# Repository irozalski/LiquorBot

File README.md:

# 🤖 LiquorBot

### Automatic liquor dispensing machine  used for pouring several-layer shots.<br> 
### The project uses a stepper motor, liquid pumps, Hall sensor, optocouplers and LEDs controlled by the Esp32 microcontroller. <br>
### Most of the case parts were printed on a 3D printer.
---
## Electronic schematic <br> 

---
## PCB 3D visualisation <br> 

---

## Render of project <br>

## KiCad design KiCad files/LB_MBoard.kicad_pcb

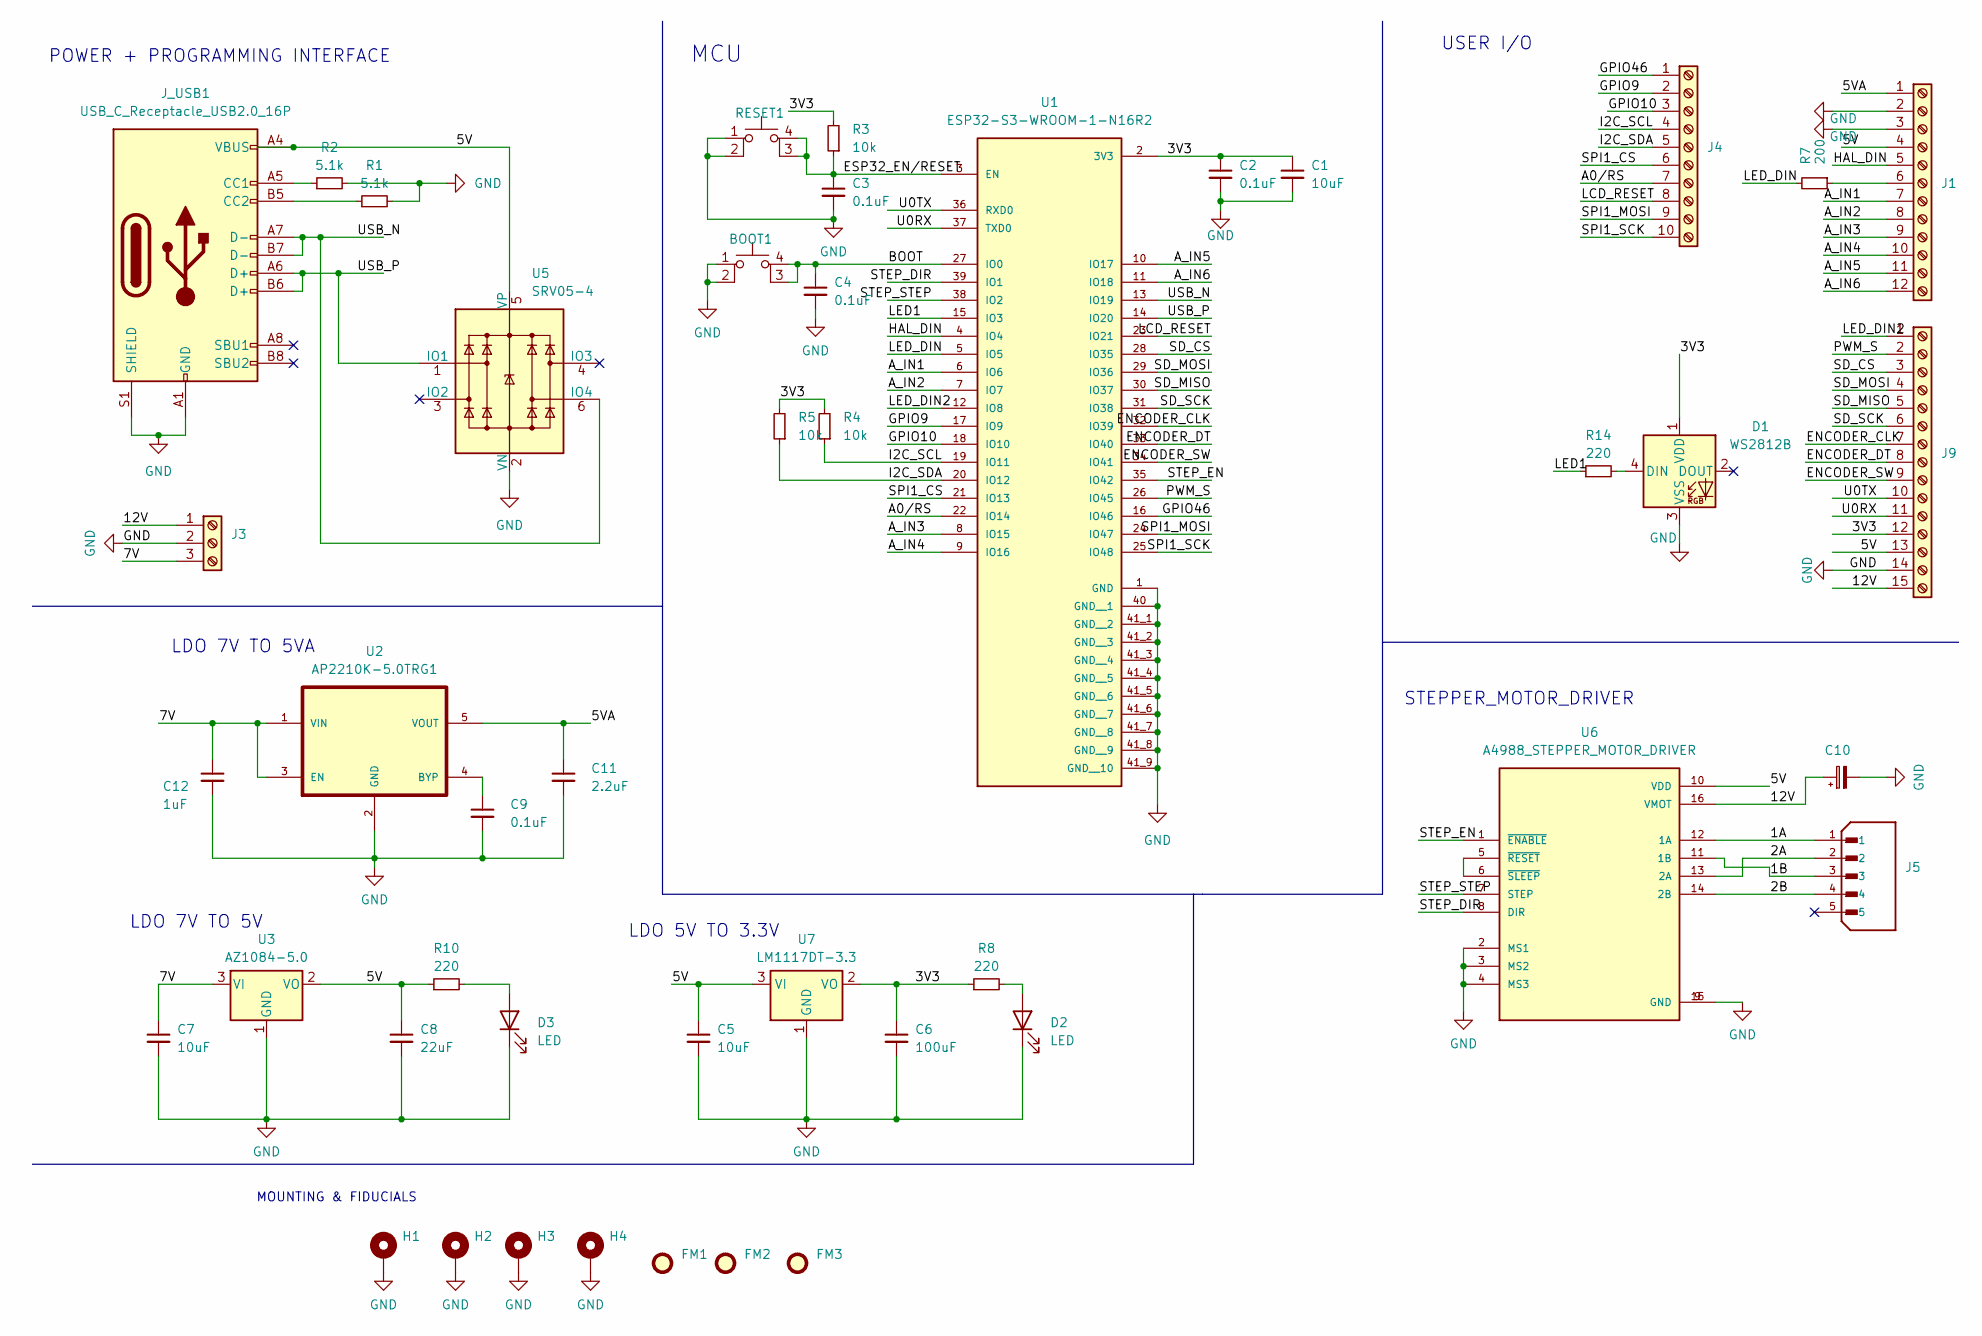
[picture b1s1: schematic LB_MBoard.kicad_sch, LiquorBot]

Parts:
BOOT1: SW_MEC_5E; SW_PTS_647_SN50_SMTR2_LFS
C1, C5, C7: 10uF; C_0805_2012Metric
C2, C3, C4, C9: 0.1uF; C_0805_2012Metric
C6: 100uF; C_0805_2012Metric
C8: 22uF; C_0805_2012Metric
C10: 100u; CAP_EEE1VA101XP
C11: 2.2uF; C_0805_2012Metric
C12: 1uF; C_0805_2012Metric
D1: WS2812B; LED_WS2812B_PLCC4_5.0x5.0mm_P3.2mm
D2, D3: LED; LED_0805_2012Metric
FM1, FM2, FM3: Fiducial; Fiducial_1mm_Mask2mm
H1, H2, H3, H4: MountingHole_Pad; MountingHole_3.2mm_M3_Pad_Via
J1: Screw_Terminal_01x12; 393570012
J3: Screw_Terminal_01x03; TerminalBlock_Phoenix_MKDS-1,5-3_1x03_P5.00mm_Horizontal
J4: Screw_Terminal_01x10; 393570010
J5: B5B-XH-A; JST_B5B-XH-A; PARTREV 7/4/21
J9: Screw_Terminal_01x15; 393570015
J_USB1: USB_C_Receptacle_USB2.0_16P; GCT_USB4085-GF-A_REVB
R1, R2: 5.1k; R_0805_2012Metric
R3, R4, R5: 10k; R_0805_2012Metric
R7: 200; R_0805_2012Metric
R8, R10, R14: 220; R_0805_2012Metric
RESET1: SW_MEC_5E; SW_PTS_647_SN50_SMTR2_LFS
U1: ESP32-S3-WROOM-1-N16R2; XCVR_ESP32-S3-WROOM-1U-N16; PARTREV v1.0
U2: AP2210K-5.0TRG1; SOT-23-5_RAW
U3: AZ1084-5.0; DPAK457P1010X238-3N
U5: SRV05-4; SOT-23-6
U6: A4988_STEPPER_MOTOR_DRIVER; MODULE_A4988_STEPPER_MOTOR_DRIVER_CARRIER
U7: LM1117DT-3.3; TO-252-3_TabPin2

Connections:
/1A: J5.1, U6.12 (1A)
/1B: J5.3, U6.11 (1B)
/2A: J5.2, U6.13 (2A)
/2B: J5.4, U6.14 (2B)
/3V3: C1.1, C2.1, C6.1, D1.1 (VDD), J9.12, R3.2, R4.2, R5.2, R8.1, U1.2 (3V3), U7.2 (VO)
/5V: C5.1, C8.1, J1.4, J9.13, J_USB1.A4 (VBUS), J_USB1.A9 (VBUS), J_USB1.B4 (VBUS), J_USB1.B9 (VBUS), R10.1, U3.2 (VO), U5.5 (VP), U6.10 (VDD), U7.3 (VI)
/5VA: C11.1, J1.1, U2.5 (VOUT)
/7V: C7.1, C12.1, J3.3, U2.1 (VIN), U2.3 (EN), U3.3 (VI)
/12V: C10.1, J3.1, J9.15, U6.16 (VMOT)
/A0/RS: J4.7, U1.22 (IO14)
/A_IN1: J1.7, U1.6 (IO6)
/A_IN2: J1.8, U1.7 (IO7)
/A_IN3: J1.9, U1.8 (IO15)
/A_IN4: J1.10, U1.9 (IO16)
/A_IN5: J1.11, U1.10 (IO17)
/A_IN6: J1.12, U1.11 (IO18)
/BOOT: BOOT1.3 (K), BOOT1.4 (A), C4.1, U1.27 (IO0); also elsewhere on the board
/ENCODER_CLK: J9.7, U1.32 (IO39)
/ENCODER_DT: J9.8, U1.33 (IO40)
/ENCODER_SW: J9.9, U1.34 (IO41)
/ESP32_EN/RESET: C3.1, R3.1, RESET1.3 (K), RESET1.4 (A), U1.3 (EN); also elsewhere on the board
/GPIO9: J4.2, U1.17 (IO9)
/GPIO10: J4.3, U1.18 (IO10)
/GPIO46: J4.1, U1.16 (IO46)
/HAL_DIN: J1.5, U1.4 (IO4)
/I2C_SCL: J4.4, R4.1, U1.19 (IO11)
/I2C_SDA: J4.5, R5.1, U1.20 (IO12)
/LCD_RESET: J4.8, U1.23 (IO21)
/LED1: R14.1, U1.15 (IO3)
/LED_DIN: R7.2, U1.5 (IO5)
/LED_DIN2: J9.1, U1.12 (IO8)
/PWM_S: J9.2, U1.26 (IO45)
/SD_CS: J9.3, U1.28 (IO35)
/SD_MISO: J9.5, U1.30 (IO37)
/SD_MOSI: J9.4, U1.29 (IO36)
/SD_SCK: J9.6, U1.31 (IO38)
/SPI1_CS: J4.6, U1.21 (IO13)
/SPI1_MOSI: J4.9, U1.24 (IO47)
/SPI1_SCK: J4.10, U1.25 (IO48)
/STEP_DIR: U1.39 (IO1), U6.8 (DIR)
/STEP_EN: U1.35 (IO42), U6.1 (~ENABLE)
/STEP_STEP: U1.38 (IO2), U6.7 (STEP)
/U0RX: J9.11, U1.37 (TXD0)
/U0TX: J9.10, U1.36 (RXD0)
/USB_N: J_USB1.A7 (D-), J_USB1.B7 (D-), U1.13 (IO19), U5.6 (IO4)
/USB_P: J_USB1.A6 (D+), J_USB1.B6 (D+), U1.14 (IO20), U5.1 (IO1)
GND: BOOT1.1, BOOT1.2, C1.2, C2.2, C3.2, C4.2, C5.2, C6.2, C7.2, C8.2, C9.2, C10.2, C11.2, C12.2, D1.3 (VSS), D2.1 (K), D3.1 (K), H1.1, H2.1, H3.1, H4.1, J1.2, J1.3, J3.2, J9.14, J_USB1.A1 (GND), J_USB1.A12 (GND), J_USB1.B1 (GND), J_USB1.B12 (GND), J_USB1.S1 (SHIELD), J_USB1.S2, J_USB1.S3, J_USB1.S4, R1.2, R2.2, RESET1.1, RESET1.2, U1.1 (GND), U1.40 (GND__1), U1.41_1 (GND__2), U1.41_2 (GND__3), U1.41_3 (GND__4), U1.41_4 (GND__5), U1.41_5 (GND__6), U1.41_6 (GND__7), U1.41_7 (GND__8), U1.41_8 (GND__9), U1.41_9 (GND__10), U1.41_10, U1.41_11, U1.41_12, U1.41_13, U1.41_14, U1.41_15, U1.41_16, U1.41_17, U1.41_18, U1.41_19, U1.41_20, U1.41_21, U2.2 (GND), U3.1 (GND), U5.2 (VN), U6.2 (MS1), U6.3 (MS2), U6.4 (MS3), U6.9 (GND), U6.15 (GND), U7.1 (GND); also elsewhere on the board
unnamed: D1.4 (DIN), R14.2
unnamed: D2.2 (A), R8.2
unnamed: D3.2 (A), R10.2
unnamed: J1.6, R7.1
unnamed: J_USB1.A5 (CC1), R2.1
unnamed: J_USB1.B5 (CC2), R1.1
unnamed: C9.1, U2.4 (BYP)
unnamed: U6.5 (~RESET), U6.6 (~SLEEP)

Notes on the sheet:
USER I/O
STEPPER_MOTOR_DRIVER
MCU
LDO 7V TO 5V
MOUNTING & FIDUCIALS
LDO 5V TO 3.3V
POWER + PROGRAMMING INTERFACE
LDO 7V TO 5VA

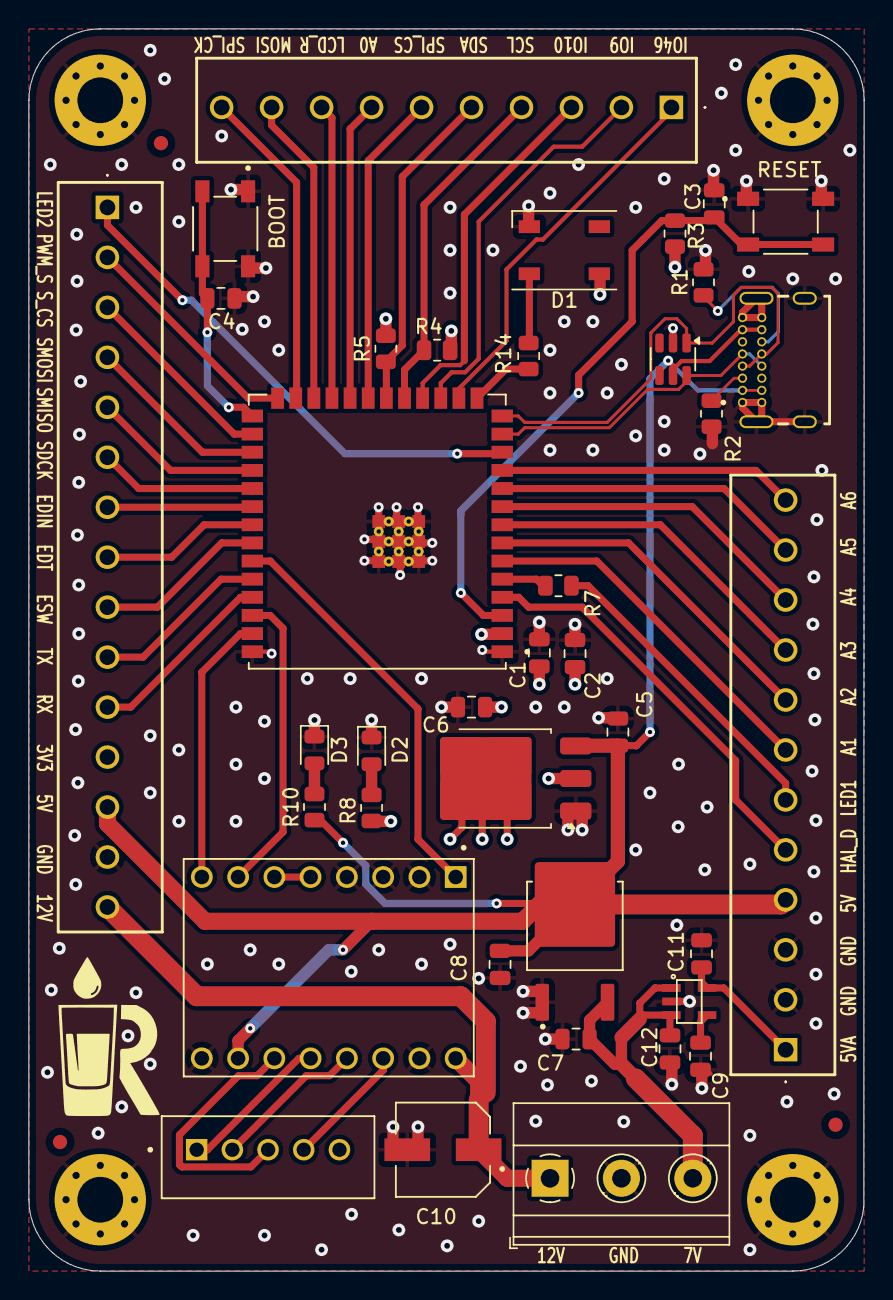
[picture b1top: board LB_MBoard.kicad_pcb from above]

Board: 4 copper layers, 58.5 x 87.0 mm, 45 parts (0 on the bottom side), 55 nets.

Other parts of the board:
BOOT: SW_MEC_5E; SW_PTS_647_SN50_SMTR2_LFS
RESET: SW_MEC_5E; SW_PTS_647_SN50_SMTR2_LFS

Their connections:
/BOOT: BOOT.3 (K), BOOT.4 (A); also elsewhere on the board
/ESP32_EN/RESET: RESET.3 (K), RESET.4 (A); also elsewhere on the board
GND: BOOT.1, BOOT.2, RESET.1, RESET.2; also elsewhere on the board

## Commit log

2023-03-22 Add files via upload
    First test version
2023-08-30 testing programs
2024-03-10 Update pouring_machine_ver1.ino
    Further testing. Pump control with the L298N H-bridge circuit was added as well as better visualization of the pouring process with LEDs.
2024-03-12 Further testing.
    Further testing. Pump and LEDs delay was added.
2024-03-13 Second pump was added, further tests.
2024-03-23 New version
    Replacement with a bipolar motor and new motor driver
2024-03-24 New version with hall effect sensor
    Hall effect sensor was added instead of step counting. Stepper motor direction is now different every time.
2024-03-28 Start animations
2024-10-04 test program
2024-11-04 Adding KiCad files
